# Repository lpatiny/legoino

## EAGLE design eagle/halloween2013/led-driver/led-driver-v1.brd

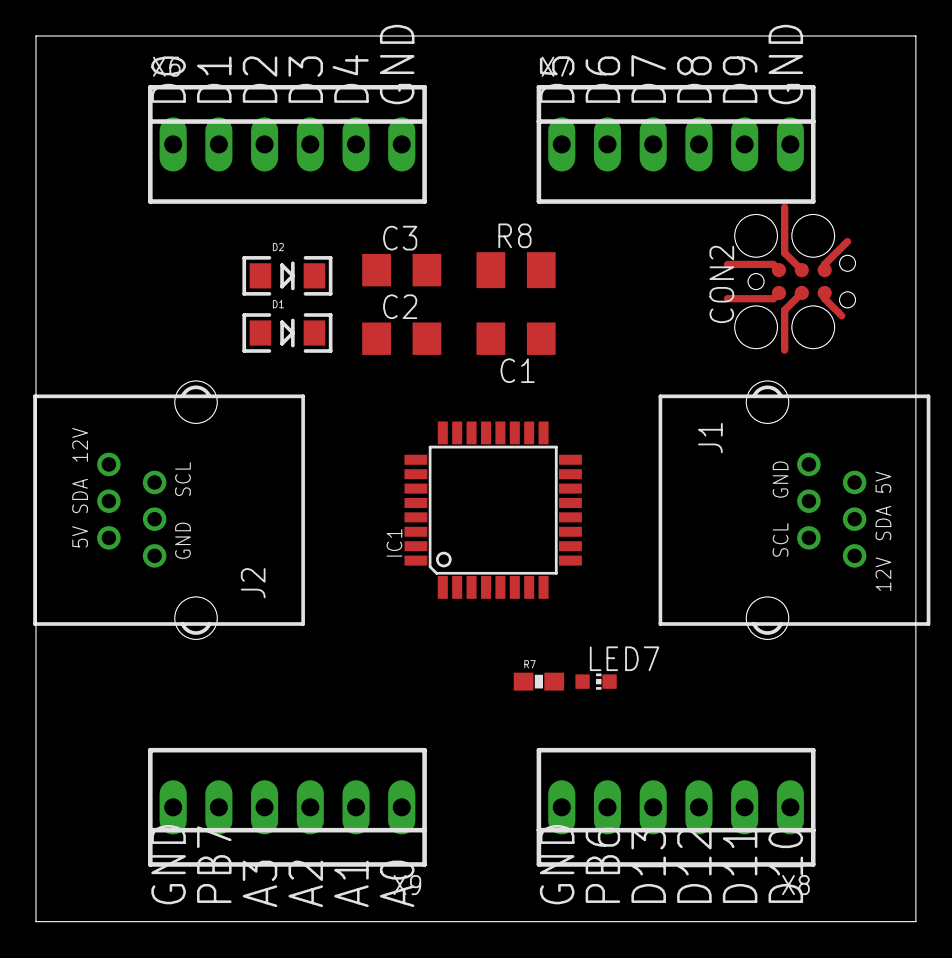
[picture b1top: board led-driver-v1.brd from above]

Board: 2 copper layers, 48.9 x 49.2 mm, 16 parts (0 on the bottom side), 30 nets.

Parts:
C1, C2: 0.1uF; C1206
C3: 10uF; C1206
CON2: TC2030-MCP
D1, D2: 1N581D1206; LED-1206
IC1: MEGA8-AI; TQFP32-08
J1, J2: RJ12RIGHTANGLE-I2C; RJ12-RIGHTANGLE-I2C
LED7: CHIP-LED0603
R7: 10k; 0603-RES
R8: 10k; M1206
X6, X7, X8, X9: 22-23-2061

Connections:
5V_A: CON2.5V, D1.A
5V_B: D2.A, J1.+5V, J2.+5V
+5V: C1.1, C2.1, C3.1, D1.C, D2.C, IC1.4, IC1.6, IC1.18, R7.1, R8.2
A0: IC1.23, X9.1
A1: IC1.24, X9.2
A2: IC1.25, X9.3
A3: IC1.26, X9.4
D0: IC1.30, X6.1
D1: IC1.31, X6.2
D2: IC1.32, X6.3
D3: IC1.1, X6.4
D4: IC1.2, X6.5
D5: IC1.9, X7.1
D6: IC1.10, X7.2
D7: IC1.11, X7.3
D8: IC1.12, X7.4
D9: IC1.13, X7.5
D10: IC1.14, X8.1
GND: C2.2, C3.2, CON2.GND, IC1.3, IC1.5, IC1.21, J1.GND1, J1.GND2, J2.GND1, J2.GND2, LED7.C, X6.6, X7.6, X8.6, X9.6
MISO: CON2.MISO, IC1.16, X8.3
MOSI: CON2.MOSI, IC1.15, X8.2
unnamed: C1.2, IC1.20
unnamed: J1.+12V, J2.+12V
unnamed: LED7.A, R7.2
PB6: IC1.7, X8.5
PB7: IC1.8, X9.5
RESET: CON2.RESET, IC1.29, R8.1
SCK: CON2.SCK, IC1.17, X8.4
SCL: IC1.28, J1.SCL, J2.SCL
SDA: IC1.27, J1.SDA, J2.SDA

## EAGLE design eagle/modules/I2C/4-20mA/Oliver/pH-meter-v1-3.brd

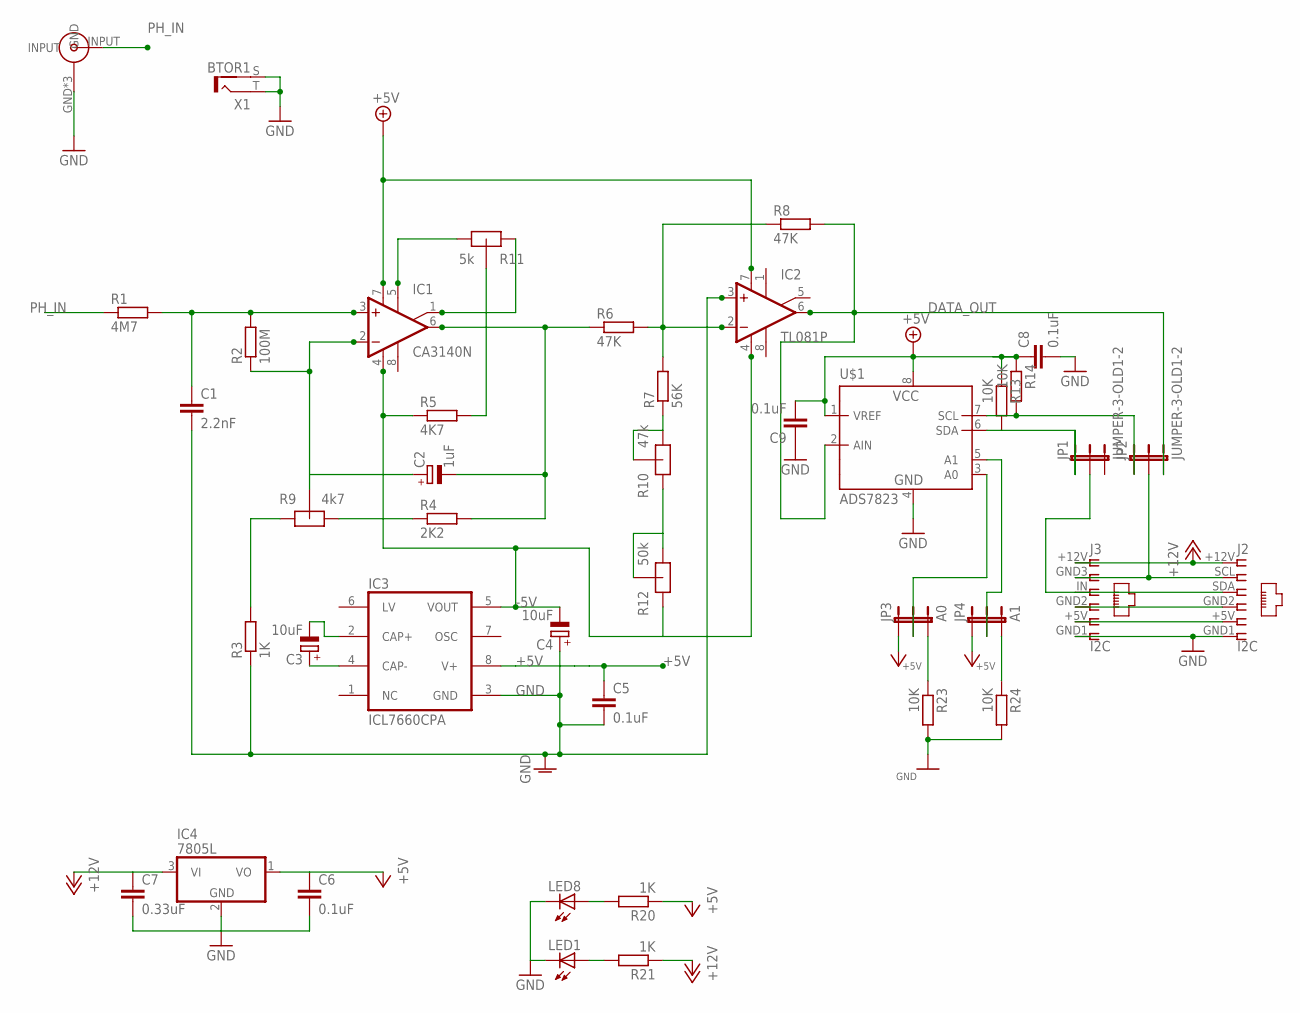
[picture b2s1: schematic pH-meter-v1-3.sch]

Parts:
C1: 2.2nF; C025-030X050
C2: 1uF; E2-4
C3, C4: 10uF; E2-4
C5, C6, C8, C9: 0.1uF; C025-030X050
C7: 0.33uF; C025-030X050
IC1: CA3140N; DIL08
IC2: TL081P; DIL08
IC3: ICL7660CPA; DIL08
IC4: 7805L; TO92
J2: I2C; RJ12-STRAIGHT-I2C
J3: I2C; RJ12-STRAIGHT-ANALOG
JP1, JP2: JUMPER-3-OLD1-2; SJ_3_PASTE1&2
JP3: A0; SJ_3_PASTE1&2
JP4: A1; SJ_3_PASTE1&2
LED1, LED8: LED3MM
R1: 4M7; 0309/12
R2: 100M; 0309/12
R3, R20, R21: 1K; 0309/12
R4: 2K2; 0309/12
R5: 4K7; 0309/12
R6, R8: 47K; 0309/12
R7: 56K; 0309/12
R9: 4k7; POT-METER_ALPS
R10: 47k; POT-METER_ALPS
R11: 5k; POT-METER_ALPS
R12: 50k; POT-METER_ALPS
R13, R14: 10K; R1206
R23, R24: 10K; 0309/12
U$1: ADS7823; MSOP8
U$2: BNC_IN; BNC_VERTICAL_AMPHENOL
X1: BTOR1

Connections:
+5V: C5.1, C6.1, C8.1, C9.2, IC1.7 (V+), IC2.7 (V+), IC3.8 (V+), IC4.1 (VO), JP3.1, JP4.1, R13.1, R14.1, R20.1, U$1.1 (VREF), U$1.8 (VCC)
+12V: C7.1, IC4.3 (VI), J2.+12V (1), J3.+12V (1), R21.1
-5V: C4.-, IC1.4 (V-), IC2.4 (V-), IC3.5 (VOUT), R5.1, R12.P$1 (IN)
ASDF: R3.2, R9.P$1 (IN)
DATA_OUT: IC2.6 (OUT), JP2.3, R8.2, U$1.2 (AIN)
GND: C1.2, C4.+, C5.2, C6.2, C7.2, C8.2, C9.1, IC2.3 (+IN), IC3.3 (GND), IC4.2 (GND), J2.GND1 (6), J2.GND2 (4), J3.GND1 (6), J3.GND2 (4), LED1.K (C), LED8.K (C), R3.1, R23.2, R24.2, U$1.4 (GND), U$2.GND, U$2.GND_1 (GND), U$2.GND_2 (GND), X1.S (2), X1.T (1)
unnamed: C1.1, IC1.3 (+IN), R1.2, R2.2
unnamed: C2.+, IC1.2 (-IN), R2.1, R9.P$2 (DRIVE)
unnamed: R5.2, R11.P$2 (DRIVE)
unnamed: IC1.5 (ON), R11.P$3 (OUT)
unnamed: IC1.1 (ON/CMP), R11.P$1 (IN)
unnamed: C2.-, IC1.6 (OUT), R4.2, R6.1
unnamed: R4.1, R9.P$3 (OUT)
unnamed: R7.1, R10.P$2 (DRIVE), R10.P$3 (OUT)
unnamed: R10.P$1 (IN), R12.P$2 (DRIVE), R12.P$3 (OUT)
unnamed: C3.-, IC3.2 (CAP+)
unnamed: IC2.2 (-IN), R6.2, R7.2, R8.1
unnamed: C3.+, IC3.4 (CAP-)
unnamed: JP1.1, R13.2, U$1.6 (SDA)
unnamed: JP2.1, R14.2, U$1.7 (SCL)
unnamed: JP3.3, R23.1
unnamed: JP4.3, R24.1
unnamed: LED8.A, R20.2
unnamed: JP3.2, U$1.3 (A0)
unnamed: JP4.2, U$1.5 (A1)
unnamed: LED1.A, R21.2
PH_IN: R1.1, U$2.INPUT
RJ12-5V: J2.+5V (5), J3.+5V (5)
SCL: J2.SCL (2), J3.GND3 (2), JP2.2
SDA: J2.SDA (3), J3.IN (3), JP1.2

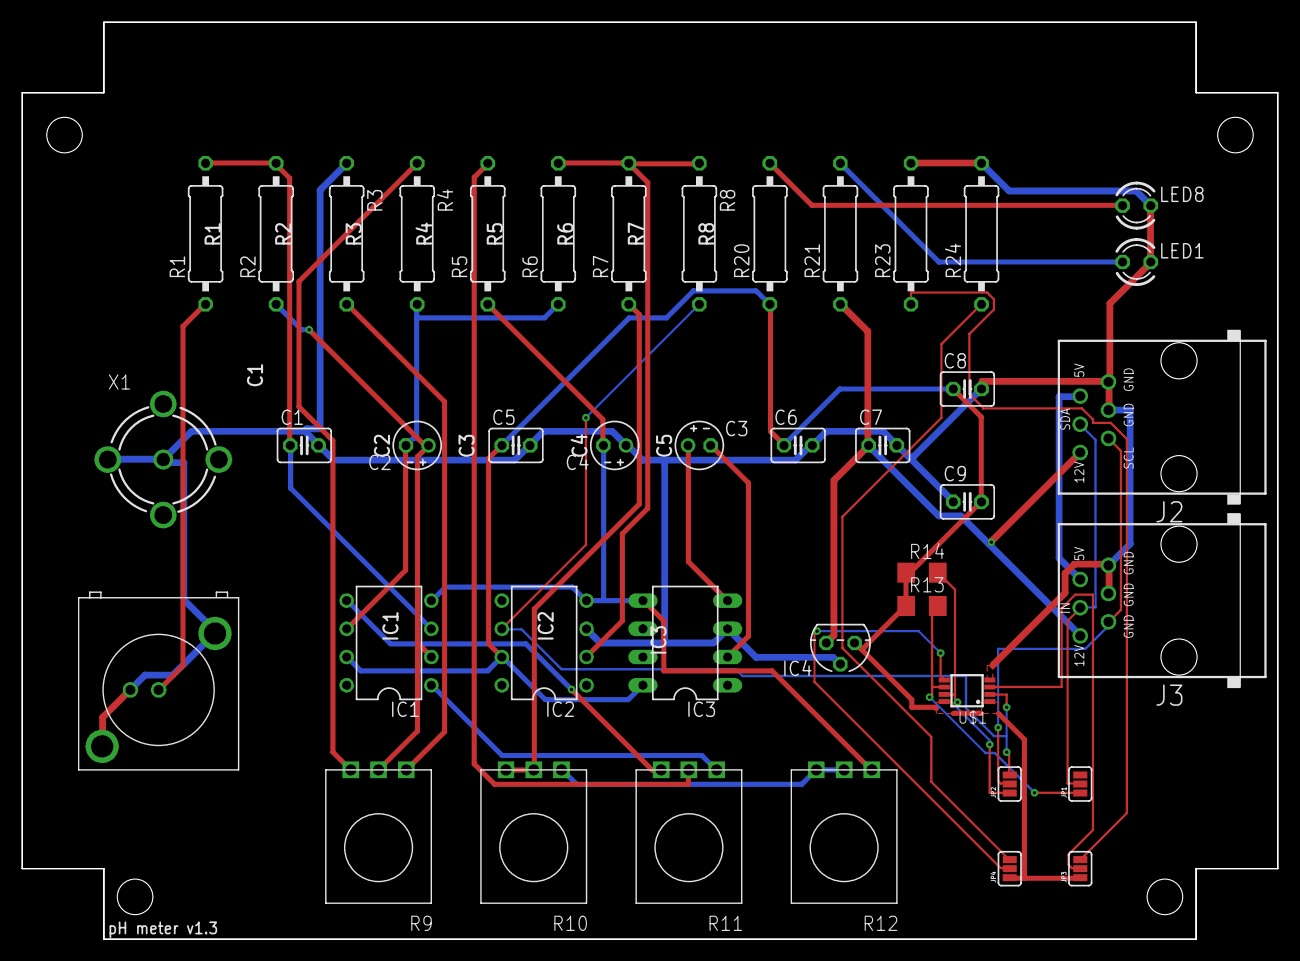
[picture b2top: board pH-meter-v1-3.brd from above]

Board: 2 copper layers, 113.0 x 82.5 mm, 42 parts (0 on the bottom side), 30 nets.

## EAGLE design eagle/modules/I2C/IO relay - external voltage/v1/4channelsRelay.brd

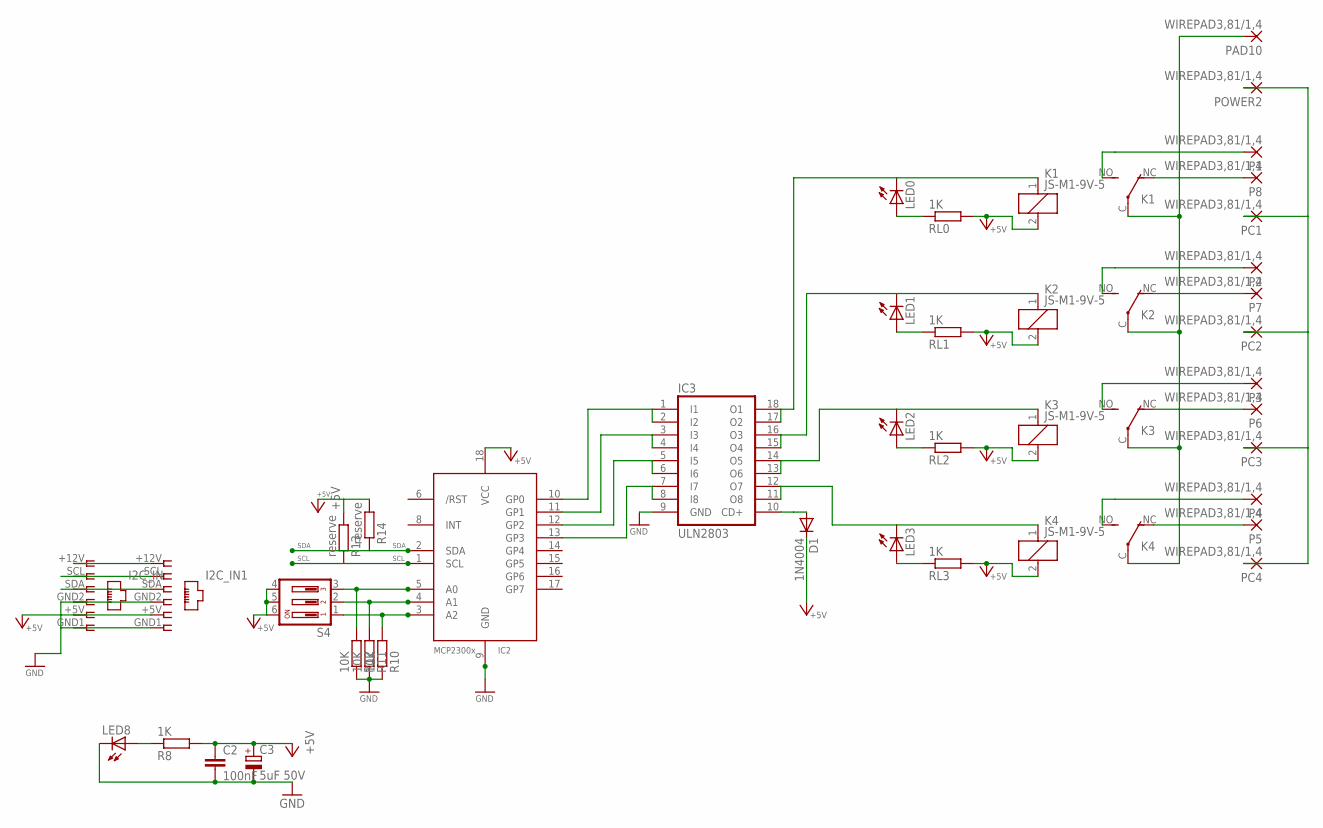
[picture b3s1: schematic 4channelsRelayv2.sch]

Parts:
C2: 100nF; C1206
C3: 5uF 50V; E3,5-8
D1: 1N4004; DO41-10
I2C_IN: I2C 1; RJ12-STRAIGHT-I2C
I2C_IN1: I2C 2; RJ12-STRAIGHT-I2C
IC2: MCP2300X/P; DIL18
IC3: ULN2803; DIL18
K1, K2, K3, K4: JS-M1-9V-5; JS-M
LED0, LED1, LED2, LED3, LED8: LED3MM
P1, P2, P3, P4, P5, P6, P7, P8: WIREPAD3,81/1,4; 3,81/1,4
PAD10: WIREPAD3,81/1,4; 3,81/1,4
PC1, PC2, PC3, PC4: WIREPAD3,81/1,4; 3,81/1,4
POWER2: WIREPAD3,81/1,4; 3,81/1,4
R8: 1K; M1206
R10, R11, R12: 10K; M1206
R13, R14: reserve; M1206
RL0, RL1, RL2, RL3: 1K; M1206
S4: DIP03YL

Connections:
+5V: C2.1, C3.+, D1.C, I2C_IN.+5V (5), I2C_IN1.+5V (5), IC2.18 (VCC), K1.2, K2.2, K3.2, K4.2, R8.2, R13.2, R14.2, RL0.2, RL1.2, RL2.2, RL3.2, S4.4, S4.5, S4.6; also elsewhere on the board
CD+: D1.A, IC3.10 (CD+)
GND: C2.2, C3.-, I2C_IN.GND1 (6), I2C_IN.GND2 (4), I2C_IN1.GND1 (6), I2C_IN1.GND2 (4), IC2.9 (GND), IC3.9 (GND), LED8.K (C), R10.1, R11.1, R12.1
unnamed: IC3.15 (O4), IC3.16 (O3), K2.1, LED1.K (C)
unnamed: LED0.A, RL0.1
unnamed: IC3.17 (O2), IC3.18 (O1), K1.1, LED0.K (C)
unnamed: LED1.A, RL1.1
unnamed: I2C_IN.+12V (1), I2C_IN1.+12V (1)
unnamed: K1.NC (O), P8.1
unnamed: K2.NC (O), P7.1
unnamed: K4.NO (S), P4.1
unnamed: IC3.11 (O8), IC3.12 (O7), K4.1, LED3.K (C)
unnamed: K3.NC (O), P6.1
unnamed: K3.NO (S), P3.1
unnamed: PC1.1, PC2.1, PC3.1, PC4.1, POWER2.1
unnamed: K4.NC (O), P5.1
unnamed: K2.NO (S), P2.1
unnamed: IC2.5 (A0), R12.2, S4.3
unnamed: IC2.4 (A1), R11.2, S4.2
unnamed: IC2.3 (A2), R10.2, S4.1
unnamed: K1.NO (S), P1.1
unnamed: LED8.A, R8.1
unnamed: LED2.A, RL2.1
unnamed: IC3.13 (O6), IC3.14 (O5), K3.1, LED2.K (C)
unnamed: LED3.A, RL3.1
P0: IC2.10 (GP0), IC3.1 (I1), IC3.2 (I2)
P1: IC2.11 (GP1), IC3.3 (I3), IC3.4 (I4)
P2: IC2.12 (GP2), IC3.5 (I5), IC3.6 (I6)
P3: IC2.13 (GP3), IC3.7 (I7), IC3.8 (I8)
POWER1: K1.C, K2.C, K3.C, K4.C, PAD10.1
SCL: I2C_IN.SCL (2), I2C_IN1.SCL (2), IC2.1 (SCL), R13.1
SDA: I2C_IN.SDA (3), I2C_IN1.SDA (3), IC2.2 (SDA), R14.1

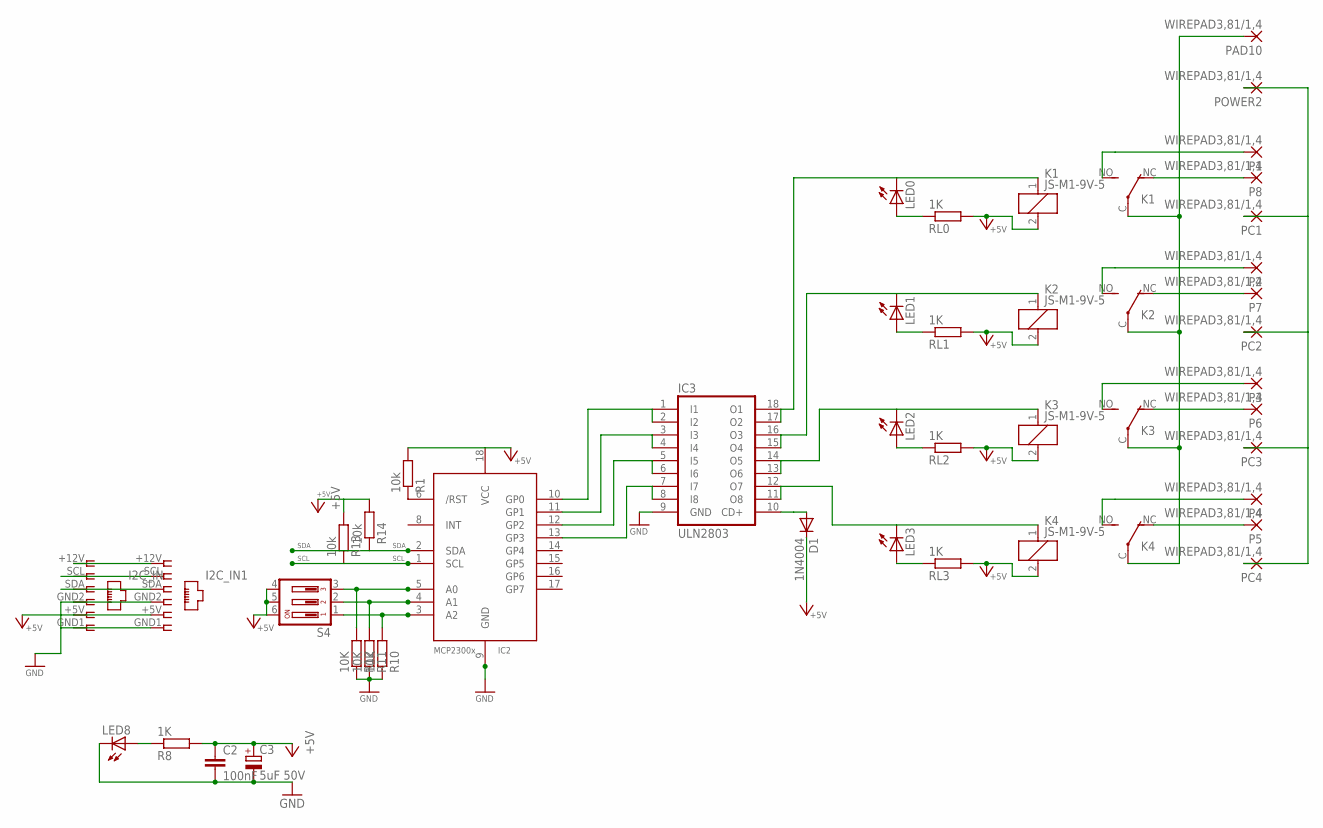
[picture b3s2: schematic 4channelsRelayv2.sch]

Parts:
C2: 100nF; C1206
C3: 5uF 50V; E3,5-8
D1: 1N4004; DO41-10
I2C_IN: I2C 1; RJ12-STRAIGHT-I2C
I2C_IN1: I2C 2; RJ12-STRAIGHT-I2C
IC2: MCP2300X/P; DIL18
IC3: ULN2803; DIL18
K1, K2, K3, K4: JS-M1-9V-5; JS-M
LED0, LED1, LED2, LED3, LED8: LED3MM
P1, P2, P3, P4, P5, P6, P7, P8: WIREPAD3,81/1,4; 3,81/1,4
PAD10: WIREPAD3,81/1,4; 3,81/1,4
PC1, PC2, PC3, PC4: WIREPAD3,81/1,4; 3,81/1,4
POWER2: WIREPAD3,81/1,4; 3,81/1,4
R1, R13, R14: 10k; M1206
R8: 1K; M1206
R10, R11, R12: 10K; M1206
RL0, RL1, RL2, RL3: 1K; M1206
S4: DIP03YL

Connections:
+5V: C2.1, C3.+, D1.C, I2C_IN.+5V (5), I2C_IN1.+5V (5), IC2.18 (VCC), K1.2, K2.2, K3.2, K4.2, R1.2, R8.2, R13.2, R14.2, RL0.2, RL1.2, RL2.2, RL3.2, S4.4, S4.5, S4.6
CD+: D1.A, IC3.10 (CD+)
GND: C2.2, C3.-, I2C_IN.GND1 (6), I2C_IN.GND2 (4), I2C_IN1.GND1 (6), I2C_IN1.GND2 (4), IC2.9 (GND), IC3.9 (GND), LED8.K (C), R10.1, R11.1, R12.1
unnamed: IC3.15 (O4), IC3.16 (O3), K2.1, LED1.K (C)
unnamed: LED0.A, RL0.1
unnamed: IC3.17 (O2), IC3.18 (O1), K1.1, LED0.K (C)
unnamed: LED1.A, RL1.1
unnamed: I2C_IN.+12V (1), I2C_IN1.+12V (1)
unnamed: K1.NC (O), P8.1
unnamed: K2.NC (O), P7.1
unnamed: K4.NO (S), P4.1
unnamed: IC3.11 (O8), IC3.12 (O7), K4.1, LED3.K (C)
unnamed: K3.NC (O), P6.1
unnamed: K3.NO (S), P3.1
unnamed: PC1.1, PC2.1, PC3.1, PC4.1, POWER2.1
unnamed: K4.NC (O), P5.1
unnamed: K2.NO (S), P2.1
unnamed: IC2.5 (A0), R12.2, S4.3
unnamed: IC2.4 (A1), R11.2, S4.2
unnamed: IC2.3 (A2), R10.2, S4.1
unnamed: K1.NO (S), P1.1
unnamed: LED8.A, R8.1
unnamed: LED2.A, RL2.1
unnamed: IC3.13 (O6), IC3.14 (O5), K3.1, LED2.K (C)
unnamed: LED3.A, RL3.1
unnamed: IC2.6 (/RST), R1.1
P0: IC2.10 (GP0), IC3.1 (I1), IC3.2 (I2)
P1: IC2.11 (GP1), IC3.3 (I3), IC3.4 (I4)
P2: IC2.12 (GP2), IC3.5 (I5), IC3.6 (I6)
P3: IC2.13 (GP3), IC3.7 (I7), IC3.8 (I8)
POWER1: K1.C, K2.C, K3.C, K4.C, PAD10.1
SCL: I2C_IN.SCL (2), I2C_IN1.SCL (2), IC2.1 (SCL), R13.1
SDA: I2C_IN.SDA (3), I2C_IN1.SDA (3), IC2.2 (SDA), R14.1

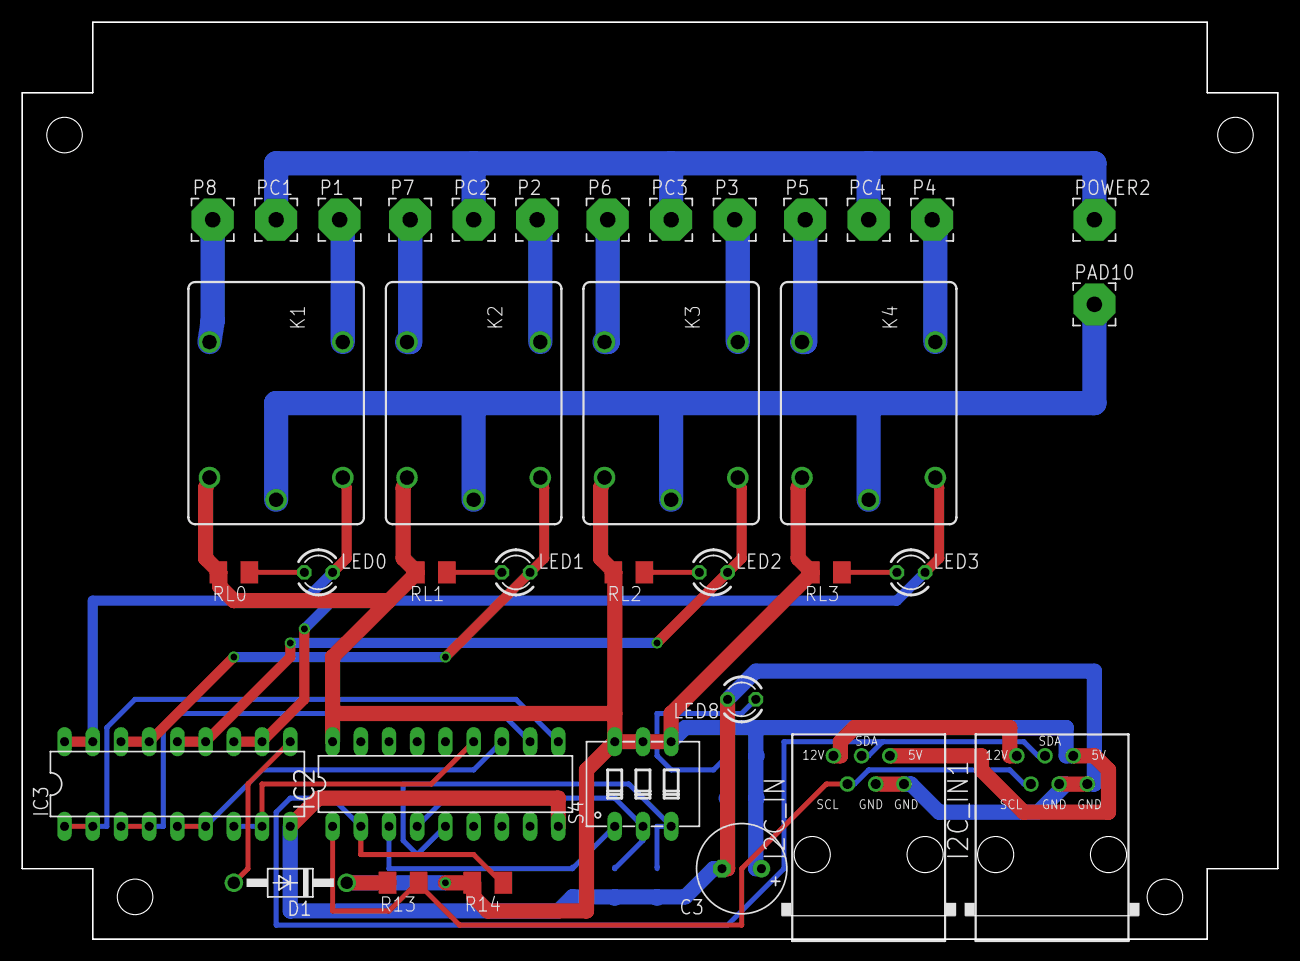
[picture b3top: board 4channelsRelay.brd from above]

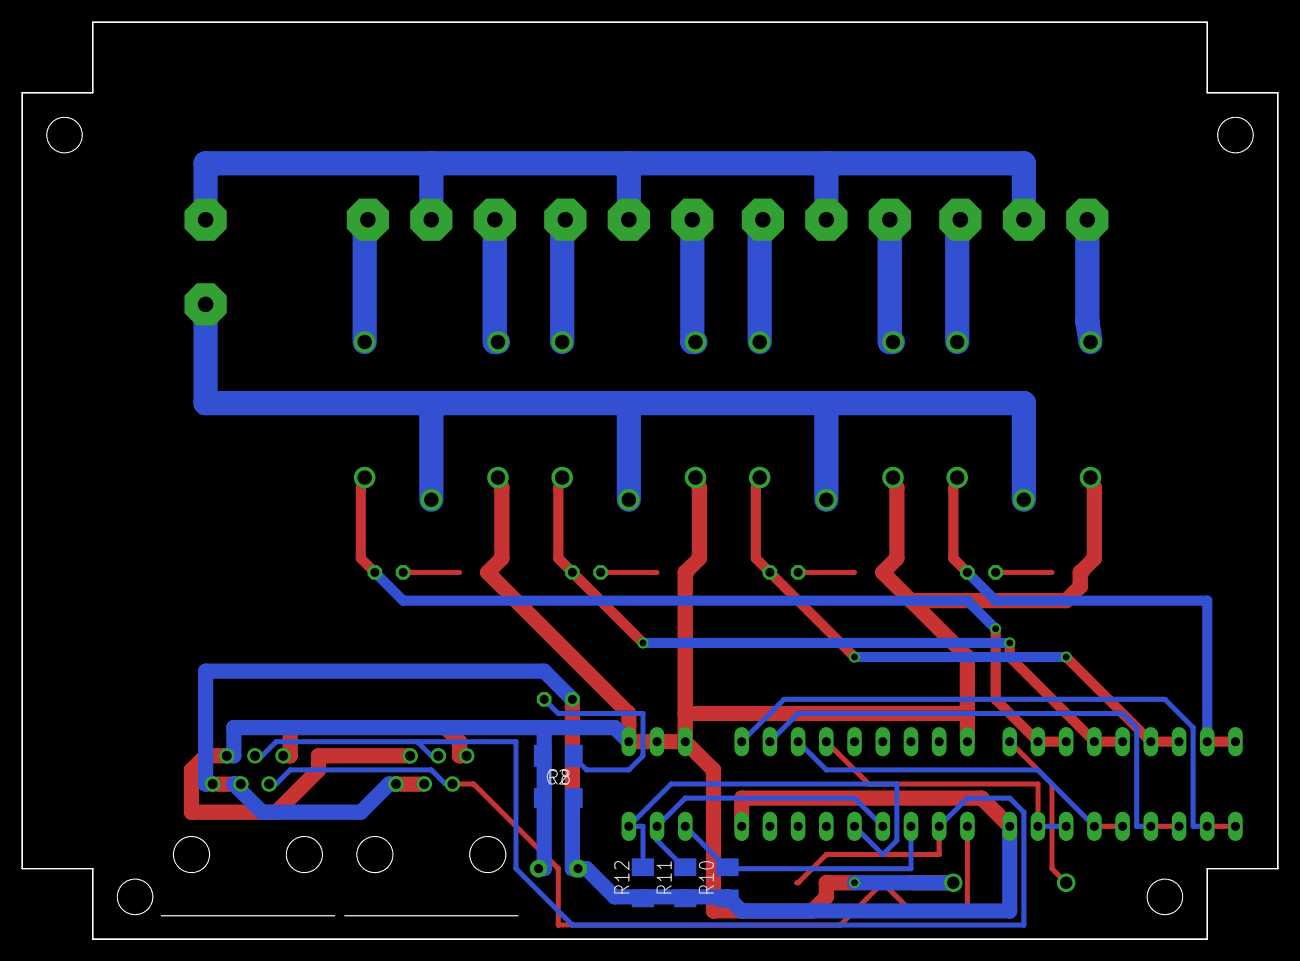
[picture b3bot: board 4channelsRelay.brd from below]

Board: 2 copper layers, 113.0 x 82.5 mm, 41 parts (5 on the bottom side), 32 nets.

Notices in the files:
parts and their libraries:
lpatiny: ©2009 ROFA.cz - modified and updated by Robert Darlington ‹rdarlington@gmail.com›
SparkFun: Licensing: CC v3.0 Share-Alike You are welcome to use this library for commercial purposes.
